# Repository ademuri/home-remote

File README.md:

This is hardware and software for an inexpensive, easy-to-build wireless remote
for controlling home automation systems. It uses RFM69 915MHz radios.

Work in progress.

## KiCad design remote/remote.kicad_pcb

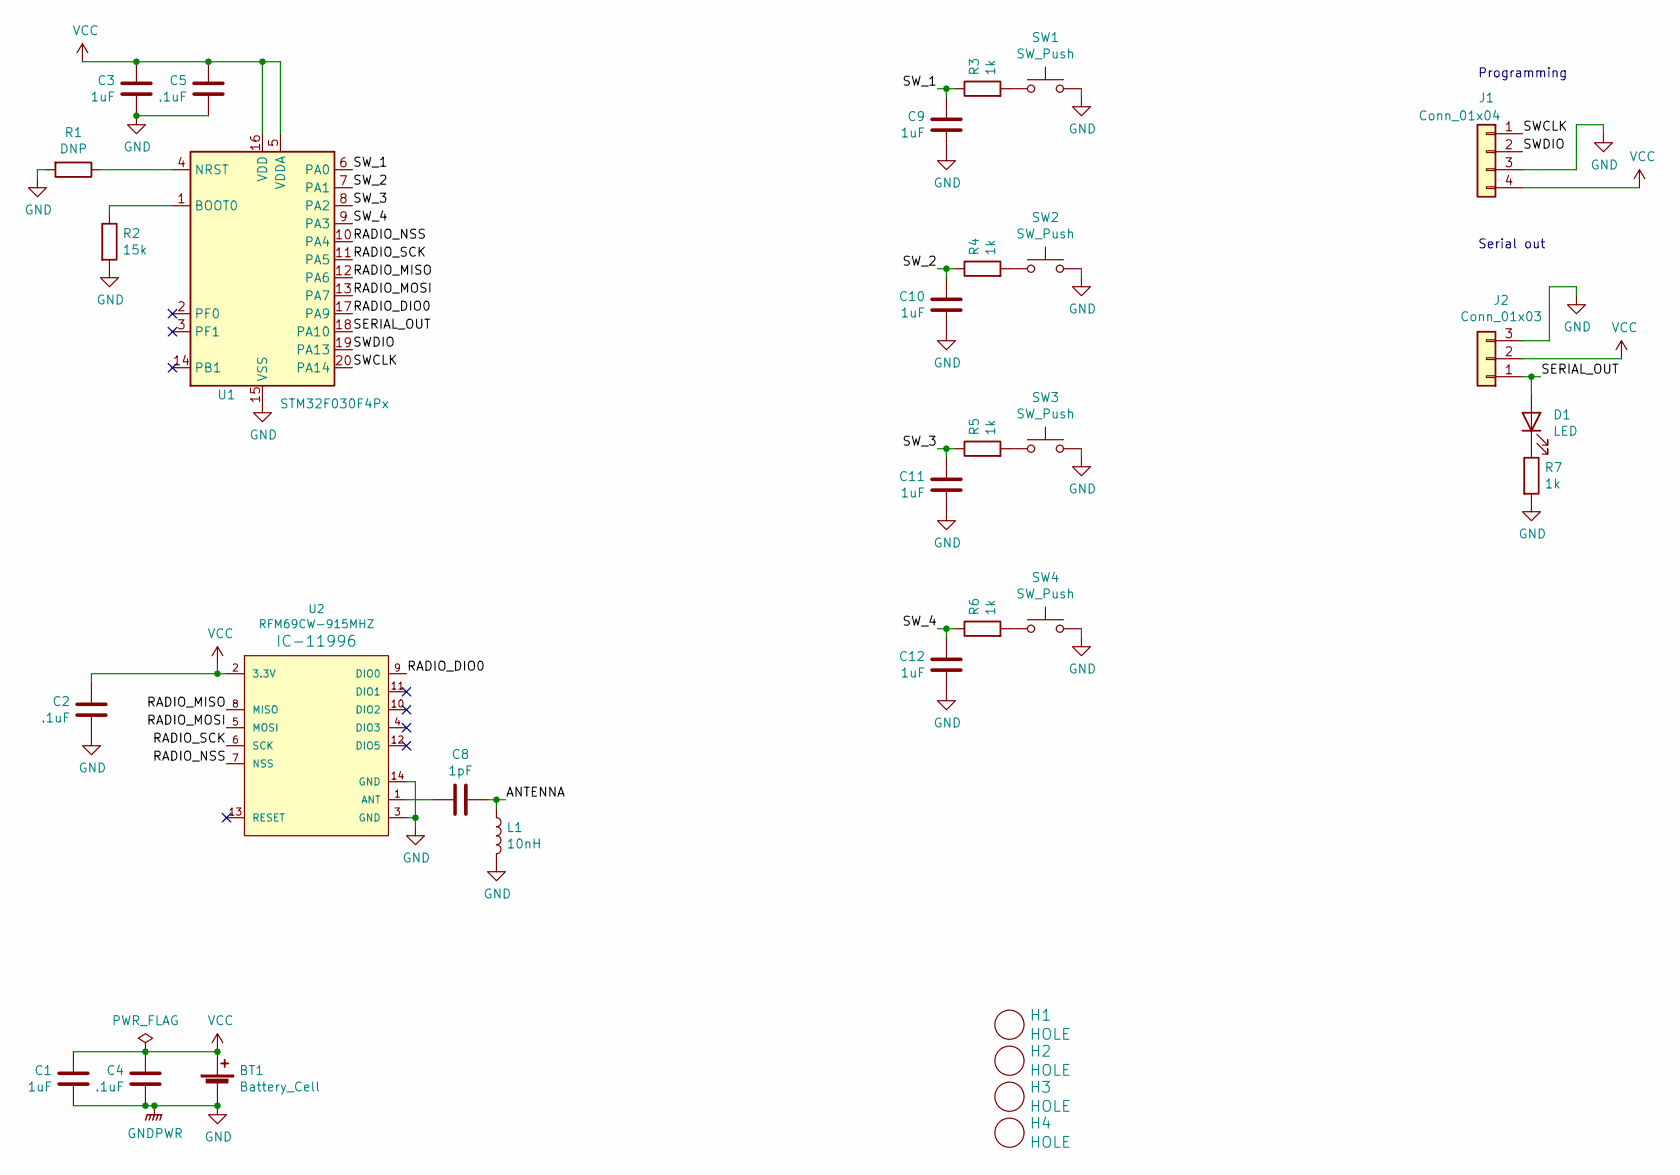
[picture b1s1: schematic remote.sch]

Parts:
BT1: Battery_Cell; BatteryHolder_Keystone_3034_1x20mm
C1, C3, C9, C10, C11, C12: 1uF; C_0402_1005Metric; LCSC C52923
C2, C4, C5: .1uF; C_0402_1005Metric; LCSC C1525
C8: 1pF; C_0402_1005Metric; LCSC C1550
D1: LED; LED_0603_1608Metric; LCSC C2286
H1, H2, H3, H4: HOLE; MountingHole_3.2mm_M3
J1: Conn_01x04; PinSocket_1x04_P2.54mm_Vertical
J2: Conn_01x03; PinSocket_1x03_P2.54mm_Vertical
L1: 10nH; L_0402_1005Metric; LCSC C27147
R1: DNP; R_0805_2012Metric_Pad1.20x1.40mm_HandSolder
R2: 15k; R_0402_1005Metric; LCSC C25756
R3, R4, R5, R6, R7: 1k; R_0402_1005Metric; LCSC C11702
SW1, SW2, SW3, SW4: SW_Push; SW_TACTILE_5.1MM_TS-1187A-C-D-B; LCSC C318889
U1: STM32F030F4Px; TSSOP-20_4.4x6.5mm_P0.65mm; LCSC C89040
U2: RFM69CW-915MHZ; RFM69CW-minimalpads

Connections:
/ANTENNA: C8.1, L1.1
/RADIO_DIO0: U1.17 (PA9), U2.9 (DIO0)
/RADIO_MISO: U1.12 (PA6), U2.8 (MISO)
/RADIO_MOSI: U1.13 (PA7), U2.5 (MOSI)
/RADIO_NSS: U1.10 (PA4), U2.7 (NSS)
/RADIO_SCK: U1.11 (PA5), U2.6 (SCK)
/SERIAL_OUT: D1.2 (A), J2.1, U1.18 (PA10)
/SWCLK: J1.1, U1.20 (PA14)
/SWDIO: J1.2, U1.19 (PA13)
/SW_1: C9.2, R3.1, U1.6 (PA0)
/SW_2: C10.2, R4.1, U1.7 (PA1)
/SW_3: C11.2, R5.1, U1.8 (PA2)
/SW_4: C12.2, R6.1, U1.9 (PA3)
GND: BT1.2 (-), C1.1, C2.1, C3.1, C4.1, C5.1, C9.1, C10.1, C11.1, C12.1, J1.3, J2.3, L1.2, R1.2, R2.2, R7.2, SW1.2, SW2.2, SW3.2, SW4.2, U1.15 (VSS), U2.3 (GND), U2.14 (GND)
unnamed: C8.2, U2.1 (ANT)
unnamed: D1.1 (K), R7.1
unnamed: R1.1, U1.4 (NRST)
unnamed: R2.1, U1.1 (BOOT0)
unnamed: R3.2, SW1.1
unnamed: R4.2, SW2.1
unnamed: R5.2, SW3.1
unnamed: R6.2, SW4.1
VCC: BT1.1 (+), C1.2, C2.2, C3.2, C4.2, C5.2, J1.4, J2.2, U1.5 (VDDA), U1.16 (VDD), U2.2 (3.3V)

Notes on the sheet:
Programming
Serial out

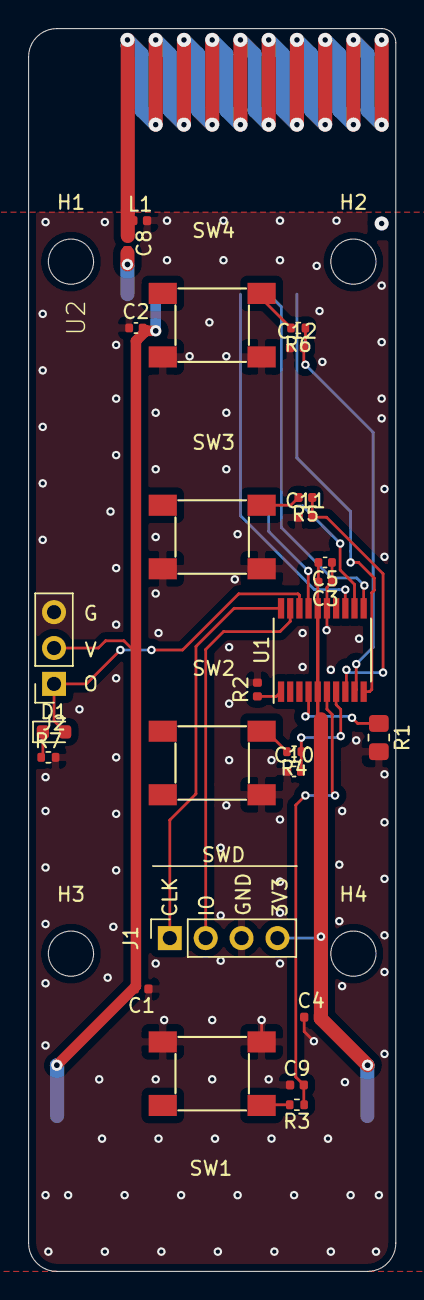
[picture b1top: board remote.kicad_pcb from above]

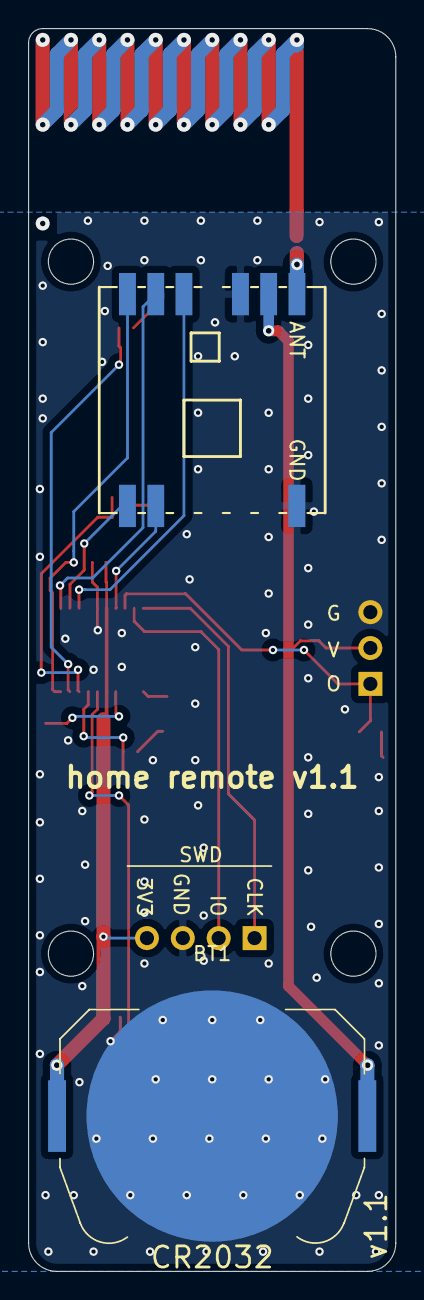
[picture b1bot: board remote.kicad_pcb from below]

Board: 2 copper layers, 26.0 x 88.0 mm, 32 parts (2 on the bottom side), 23 nets.

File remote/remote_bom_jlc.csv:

"Comment","Designator","Footprint","LCSC Part #"
"1uF","C3,C9,C1,C10,C11,C12","C_0402_1005Metric","C52923"
".1uF","C5,C4,C2","C_0402_1005Metric","C1525"
"1pF","C8","C_0402_1005Metric","C1550"
"LED","D1","LED_0603_1608Metric","C2286"
"10nH","L1","L_0402_1005Metric","C27147"
"15k","R2","R_0402_1005Metric","C25756"
"1k","R7,R3,R4,R5,R6","R_0402_1005Metric","C11702"
"SW_Push","SW1,SW2,SW3,SW4","SW_TACTILE_5.1MM_TS-1187A-C-D-B","C318889"
"STM32F030F4Px","U1","TSSOP-20_4.4x6.5mm_P0.65mm","C89040"

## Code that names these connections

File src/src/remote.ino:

#ifdef REMOTE

#include <RH_RF69.h>
#include <SPI.h>

const uint8_t kDeviceId = 1;

// Pins
// Note: including std::vector adds another ~1.8k of code, and makes the binary too big :|
const uint8_t kNumSensePins = 4;
const int kSensePins[] = {PA0, PA1, PA2, PA3};
const uint8_t kNumUnusedPins = 3;
const int kUnusedPins[] = {PF0, PF1, PB1};
const int kLed = PA10;

RH_RF69 radio(/* SS */ PA4, /* interrupt */ PA9);

volatile int8_t pressed_button = -1;

void ButtonPressed() {
  pressed_button = -1;
  for (int i = 0; i < kNumSensePins; i++) {
    if (!digitalRead(kSensePins[i])) {
      if (pressed_button > -1) {
        pressed_button = -1;
      } else {
        pressed_button = i;
      }
    }
  }
}

// Enter STM32 Stop mode - tiny current draw (with radio in sleep, measured at
// ~5.3uA), maintains RAM/program state, wakes up on external interrupts (i.e.
// button presses).
void Stop() {
  __HAL_RCC_PWR_CLK_ENABLE();
  HAL_PWR_EnableBkUpAccess();
  HAL_PWR_EnterSTOPMode(PWR_LOWPOWERREGULATOR_ON, PWR_STOPENTRY_WFI);
}

void setup() {
  pinMode(kLed, OUTPUT);
  digitalWrite(kLed, HIGH);
  for (uint8_t i = 0; i < kNumSensePins; i++) {
    pinMode(kSensePins[i], INPUT_PULLUP);
    attachInterrupt(digitalPinToInterrupt(kSensePins[i]), ButtonPressed, FALLING);
  }

  delay(5);
  radio.init();
  radio.setTxPower(0, false);
  radio.setFrequency(915.0);
  radio.sleep();

  // Delay before stopping to make programming easier
  delay(2000);

  // Set unused pins to INPUT_PULLUP so they're not floating => less power consumption
  for (uint8_t i = 0; i < kNumUnusedPins; i++) {
    pinMode(kUnusedPins[i], INPUT_PULLUP);
  }
  digitalWrite(kLed, LOW);
  Stop();
}

void loop() {
  if (pressed_button < 0) {
    int pressed = 0;
    for (int i = 0; i < kNumSensePins; i++) {
      if (!digitalRead(kSensePins[i])) {
        pressed++;
      }
    }

    if (pressed > 1) {
      // If multiple buttons pressed, don't sleep (for easier programming)
      digitalWrite(kLed, HIGH);
      delay(10000);
      digitalWrite(kLed, LOW);
      Stop();
    } else {
      Stop();
    }
  } else {
    digitalWrite(kLed, HIGH);

    // Send message
    const uint8_t packet_size = 1;
    uint8_t packet[packet_size];
    // First byte is device ID + button number
    packet[0] = (kDeviceId << 2) | (pressed_button & 0b11);
    radio.send(packet, packet_size);
    radio.waitPacketSent();
    radio.sleep();
    digitalWrite(kLed, LOW);
    Stop();
  }
}

#endif  // REMOTE

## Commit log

2020-10-06 Start adding schematic for remote
2020-10-07 WIP switch to p-channel mosfet
2020-10-08 More schematic progress - add button circuits
2020-10-09 Add simulation for remote button sensing
2020-10-09 Fix button sensing
2020-10-09 Schematic and footprint associations completed for first pass
2020-10-09 Add metadata
2020-10-11 Start layout - outline and easy placement
2020-10-12 Start laying out - antenna and power
2020-10-13 Add PDF of schematic
2020-10-17 Finish remote v1.0
2020-10-25 Add scaffolding for remote software
2020-10-25 Add (untested) code for remote
2020-10-25 Add scaffolding for gateway
2020-10-25 Add travis config to build PlatformIO code
2020-10-25 Cache pip in travis
2020-11-03 Implement remote
2020-11-05 Implement gateway
2020-11-05 Re-initialize the gateway when serial disconnects
2020-11-05 Cleanup unused delay
2020-11-08 Only sleep if a button is pressed.
    This makes it much easier to program the device, since when it's powered
    from the programmer no button will be pressed.
2020-11-08 Add support for cycling through presets.
2020-12-06 Make remote more reliable.
    Leave LED on so that the decoupling caps drain more quickly - without
    this, if you press the button too quickly it won't detect it. Also delay
    a bit at startup.
2020-12-06 Update schematic for hardware v1.1:
    - Change to always-on, using interrupts to detect button presses
    - Expose pads for easy resetting
    - Leave an analog-capable pin unconnected, for random seeding
2020-12-06 Update code for hardware v1.1 (untested)
2020-12-06 Remove preset logic from gateway.
    This will live in Home Assistant/Node RED instead.
2020-12-06 Add node-red flow for dimmer
2020-12-06 Add status LED
2020-12-06 Add wall plate mount
2020-12-07 Fix wall plate
2020-12-10 Update code for v1.1 with actual hardware testing
